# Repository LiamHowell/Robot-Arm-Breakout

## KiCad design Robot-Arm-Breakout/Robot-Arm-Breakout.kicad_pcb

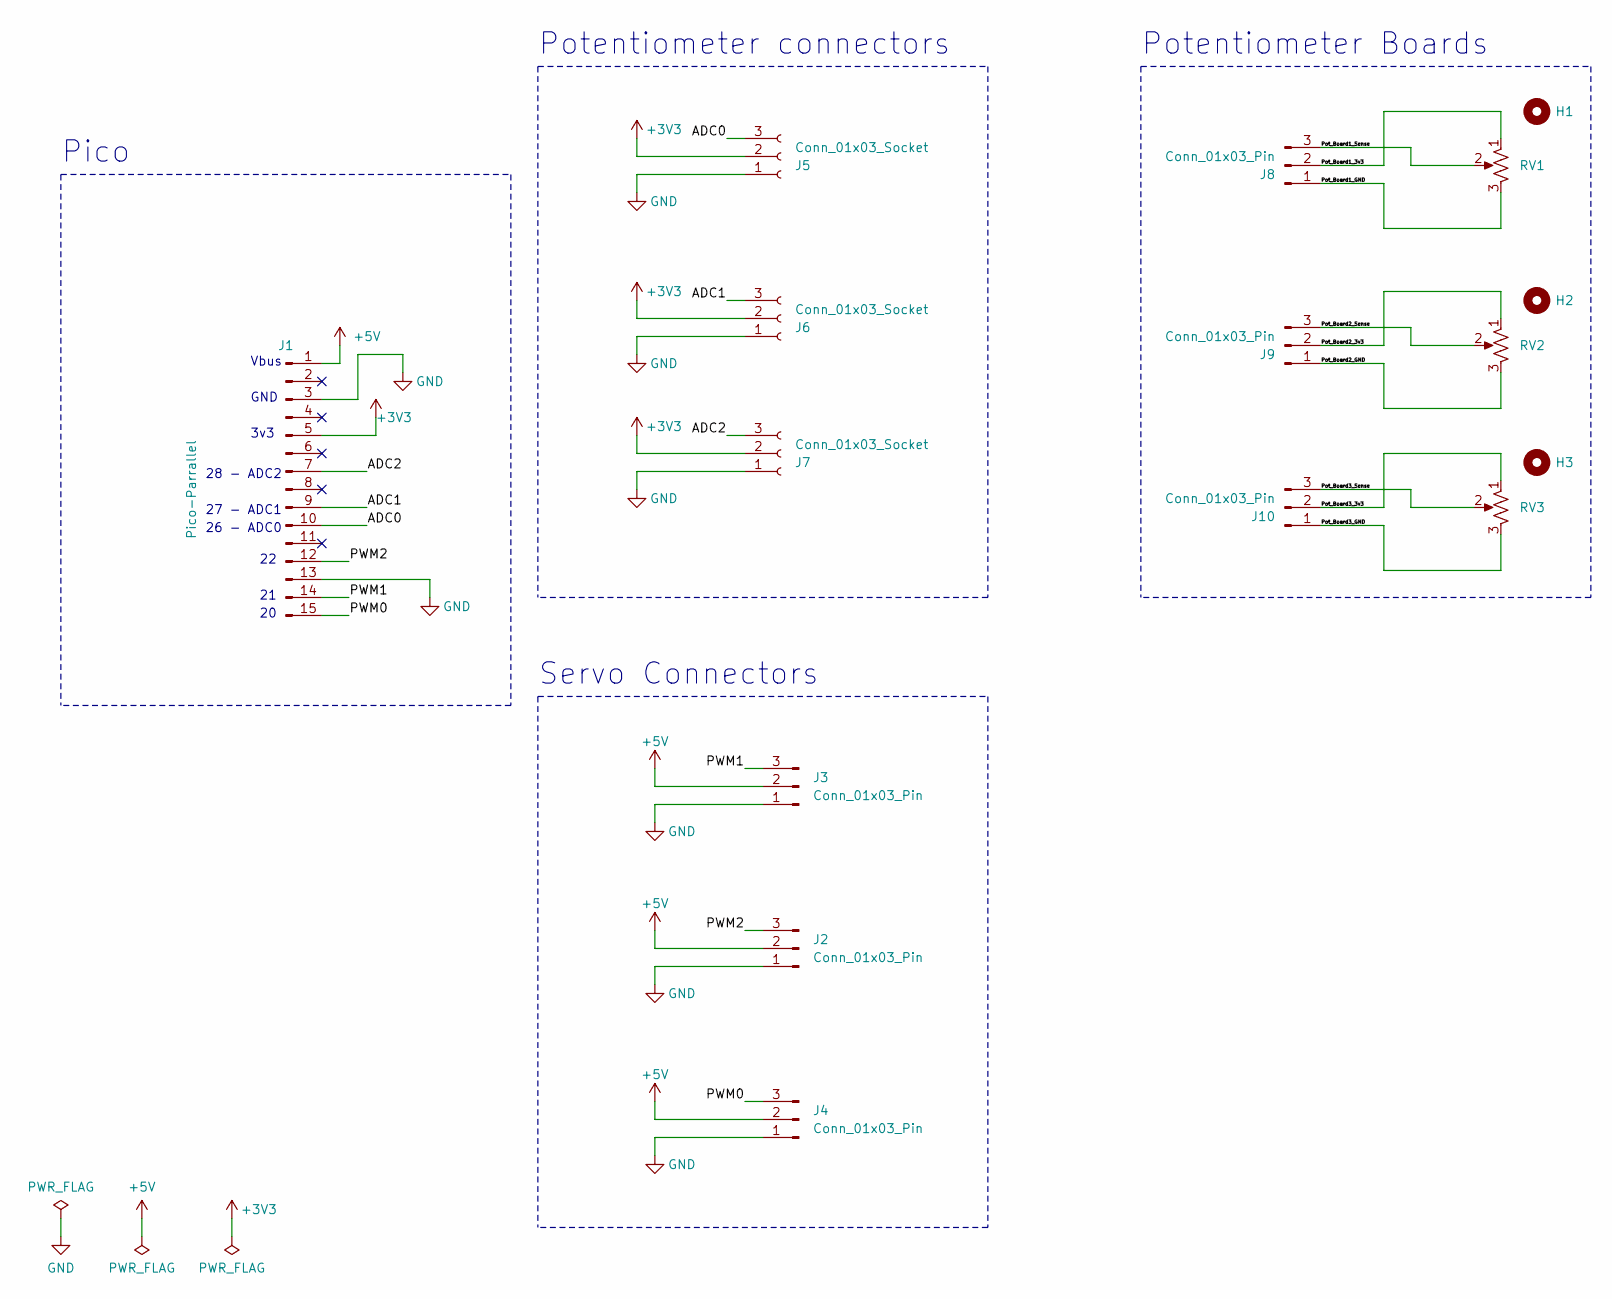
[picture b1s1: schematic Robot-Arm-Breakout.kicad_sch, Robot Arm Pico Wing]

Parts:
H1, H2, H3: MountingHole; MountingHole_3.2mm_M3
J1: Pico-Parrallel; PinSocket_1x15_P2.54mm_Vertical
J2, J3, J4: Conn_01x03_Pin; PinSocket_1x03_P2.54mm_Vertical
J5, J6, J7: Conn_01x03_Socket; PinSocket_1x03_P2.54mm_Vertical
J8, J9, J10: Conn_01x03_Pin; PinHeader_1x03_P2.54mm_Horizontal
RV1, RV2, RV3: R_Potentiometer_US; Potentiometer-Multi

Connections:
+3V3: J1.5, J5.2, J6.2, J7.2
+5V: J1.1, J2.2, J3.2, J4.2
/ADC0: J1.10, J5.3
/ADC1: J1.9, J6.3
/ADC2: J1.7, J7.3
/PWM0: J1.15, J4.3
/PWM1: J1.14, J3.3
/PWM2: J1.12, J2.3
/Pot_Board1_3v3: J8.2, RV1.1
/Pot_Board1_GND: J8.1, RV1.3
/Pot_Board1_Sense: J8.3, RV1.2
/Pot_Board2_3v3: J9.2, RV2.1
/Pot_Board2_GND: J9.1, RV2.3
/Pot_Board2_Sense: J9.3, RV2.2
/Pot_Board3_3v3: J10.2, RV3.1
/Pot_Board3_GND: J10.1, RV3.3
/Pot_Board3_Sense: J10.3, RV3.2
GND: J1.3, J1.13, J2.1, J3.1, J4.1, J5.1, J6.1, J7.1

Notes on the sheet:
27 - ADC1
Potentiometer connectors
Vbus
GND
Pico
Potentiometer Boards
Servo Connectors
26 - ADC0
28 - ADC2
3v3

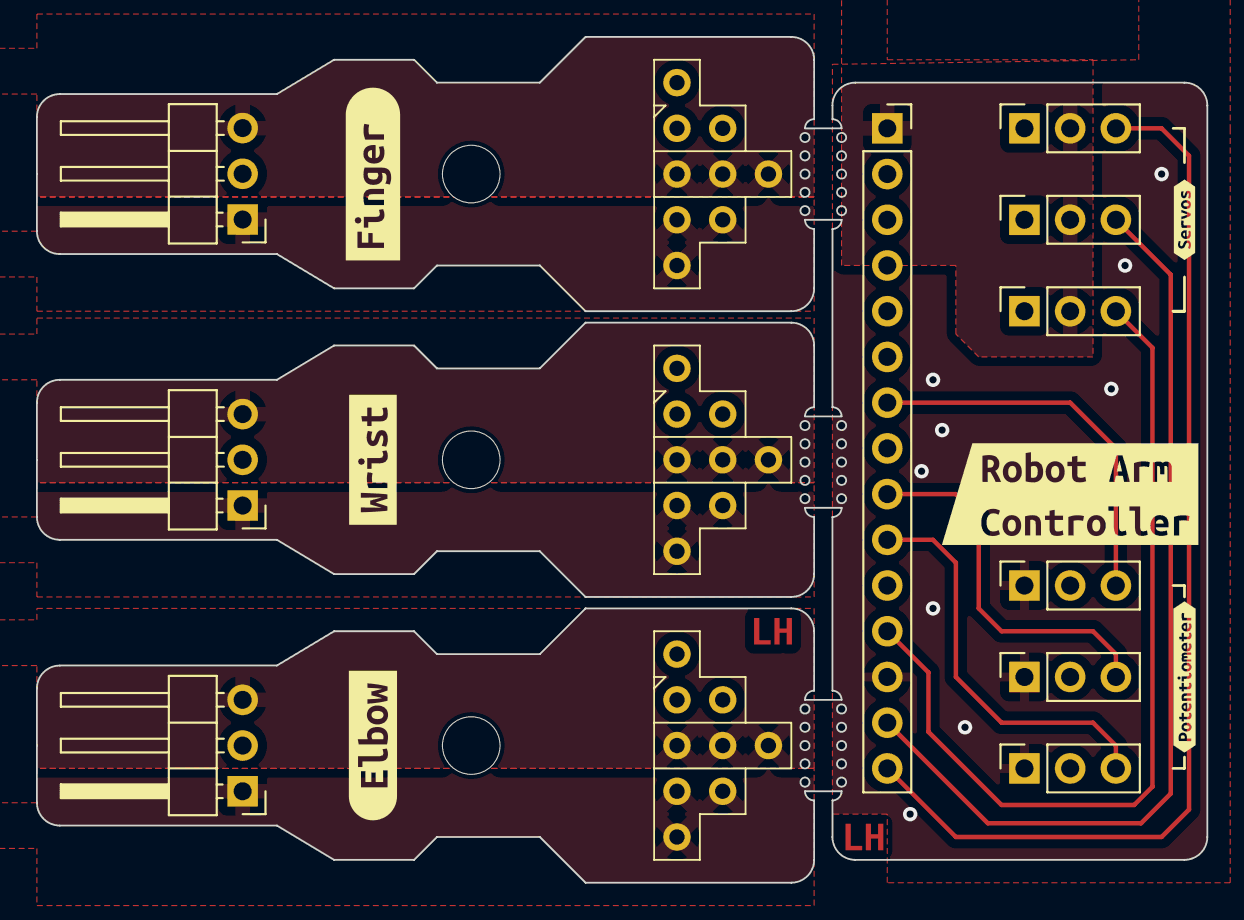
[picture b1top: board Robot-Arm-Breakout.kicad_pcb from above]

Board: 2 copper layers, 65.0 x 47.0 mm, 25 parts (1 on the bottom side), 18 nets.

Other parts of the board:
kibuzzard-65757C1E: G***; kibuzzard-65757C1E
kibuzzard-65757C16: G***; kibuzzard-65757C16
kibuzzard-65757EFB: G***; kibuzzard-65757EFB
kibuzzard-657581BB: G***; kibuzzard-657581BB
kibuzzard-6575800A: G***; kibuzzard-6575800A
kibuzzard-65758041: G***; kibuzzard-65758041
kibuzzard-65758048: G***; kibuzzard-65758048
kibuzzard-65758245, kibuzzard-65758245#2: G***; kibuzzard-65758245

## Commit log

2023-12-04 Started creating PCB
2023-12-10 Commit before Combining boards with mousebites
2023-12-11 All silkscreen done
2023-12-12 Updated PCB
